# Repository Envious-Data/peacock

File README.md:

# Peacock

Peacock is an RP2040 powered trackpad running QMK. It features an integrated Microchip MaxTouch sensor IC which is
connected to a 7" capacitive sensor.

This repo contains a fork of George Norton's project which I have modified to be a single PCB without the keyboard switches and encoders, I dont have the knowledge to have done this project myself hence why I have forked George's project.

## Features
- Fully PCBA, this other than switches and encoders, this board is designed to be fully factory assembled.
- Integrated RP2040 controller, no need to a separate controller.
- 7 inch 16:9 capacitive sensor.

## But how does it work?
The capacitive sensing IC is wired to a grid of diamond shaped electrodes. The diamonds are connected to form rows and columns. The IC scans the matrix by
applying a small voltage to the rows in turn, and then measuring voltage on the columns. Any conductive objects nearby (like your finger) will distrupt the
electrical field and can be detected.

## Software limitations
QMK currently supports pointing devices, but it reports them as USB hid mice. This means we only report a single pointer movement, a pair of scroll wheels and
a set of buttons to the host. For now, this prevents us from supporting some multitouch gestures such as pinch to zoom.

## Firmware
Peacock support has not yet been merged back to QMK. You can find a branch [here](https://github.com/george-norton/qmk_firmware/tree/peacock).

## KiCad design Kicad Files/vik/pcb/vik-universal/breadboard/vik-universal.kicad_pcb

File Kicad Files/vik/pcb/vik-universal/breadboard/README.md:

# VIK universal (breadboard)

## Overview

This is a simple pcb that allows you to connect any series of up to 12 pin headers to a VIK connector, in any order.

You solder one of the numbered through holes to a column. Be careful not to solder multiple signals from the 3rd party board to the same VIK signal (each column). Each column of through holes (except the numbered ones on the left or right) are all wired together.

## Fabrication and BOM

For PCB fabrication, you can use the files in the production folder.

* gerbers.zip - the file used to fabricate the pcb
* bom.csv - used for PCBA. You can also use the part numbers in this file to look up the exact parts as [lcsc.com](https://lcsc.com)
* positions.csv - used for PCBA

Using the 3 files above, this has been tested at [jlcpcb.com](https://jlcpcb.com)

## VIK module certification

| Category                | Classification          | Response           |
| ----------------------- | ----------------------- | ------------------ |
| FPC connector           | Required                | :heavy_check_mark: |
| Breakout pins           | Recommended             | :heavy_check_mark: |
| Uses: SPI               | Optional                | N/A                |
| SPI used for SPI only   | Strongly recommended    | N/A                |
| Uses: I2C               | Optional                | N/A                |
| I2C used for I2C only   | Strongly Recommended    | N/A                |
| I2C pull ups            | Required                | N/A                |
| Uses: RGB               | Optional                | N/A                |
| Uses: Extra GPIO 1      | Optional                | N/A                |
| Uses: Extra GPIO 2      | Optional                | N/A                |
| Standard PCB Size/Mount | Strongly recommended    | :x:                |

## PCB images

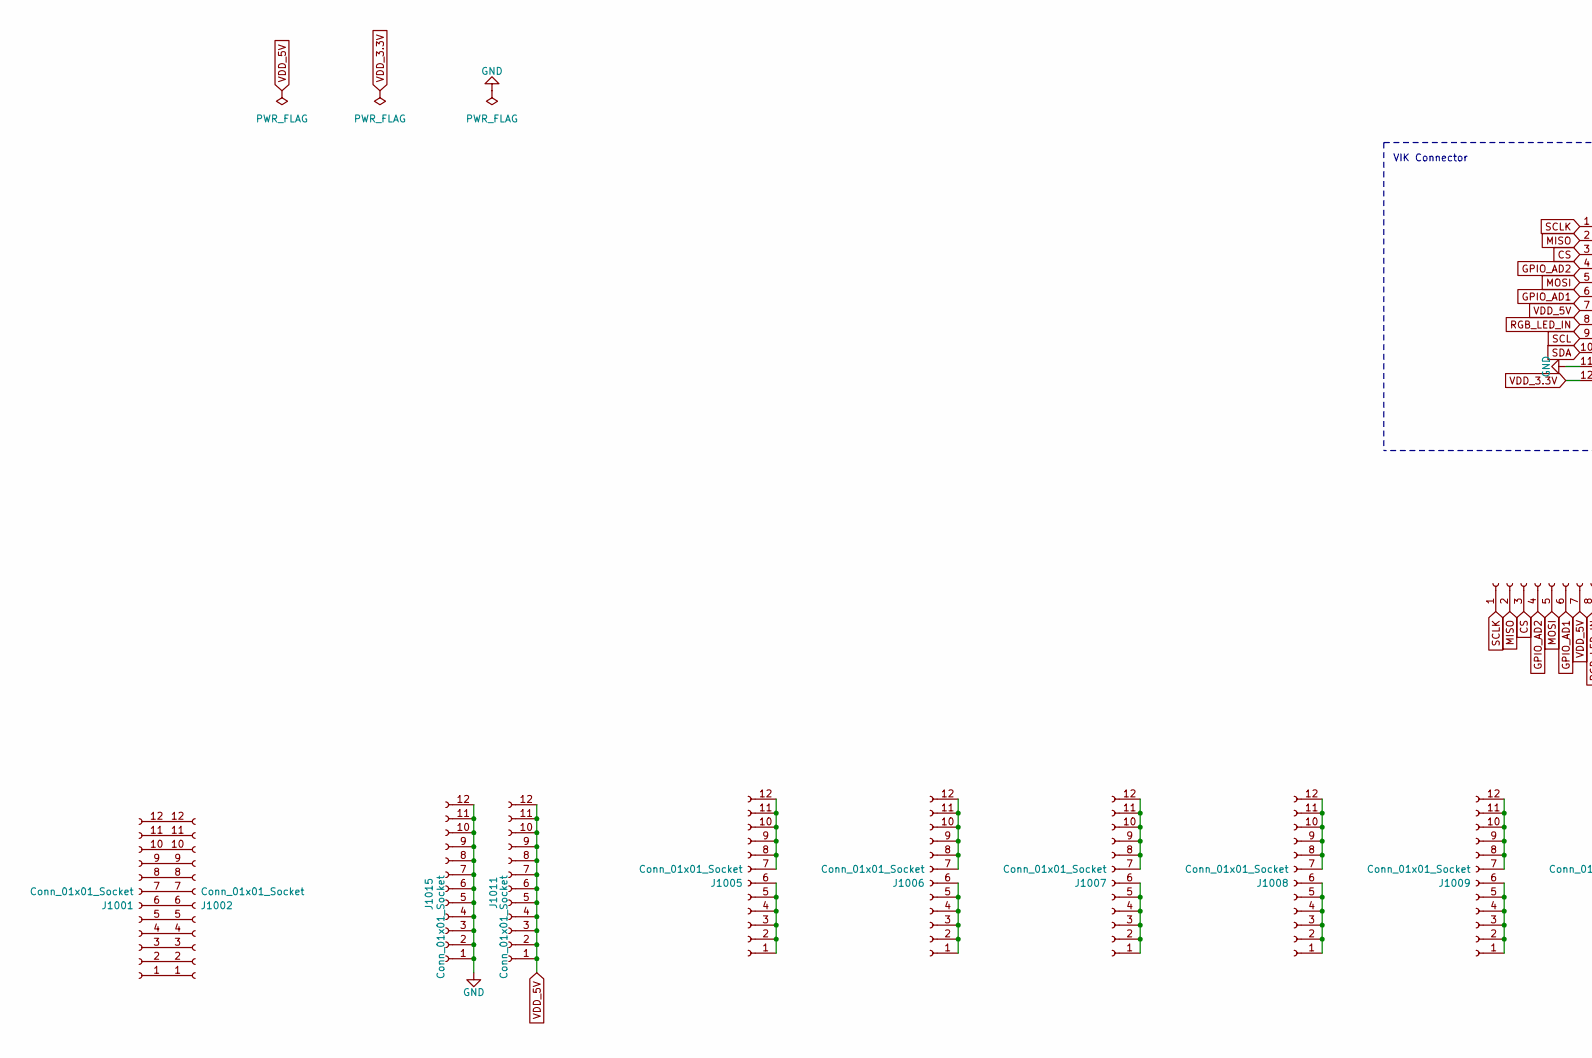
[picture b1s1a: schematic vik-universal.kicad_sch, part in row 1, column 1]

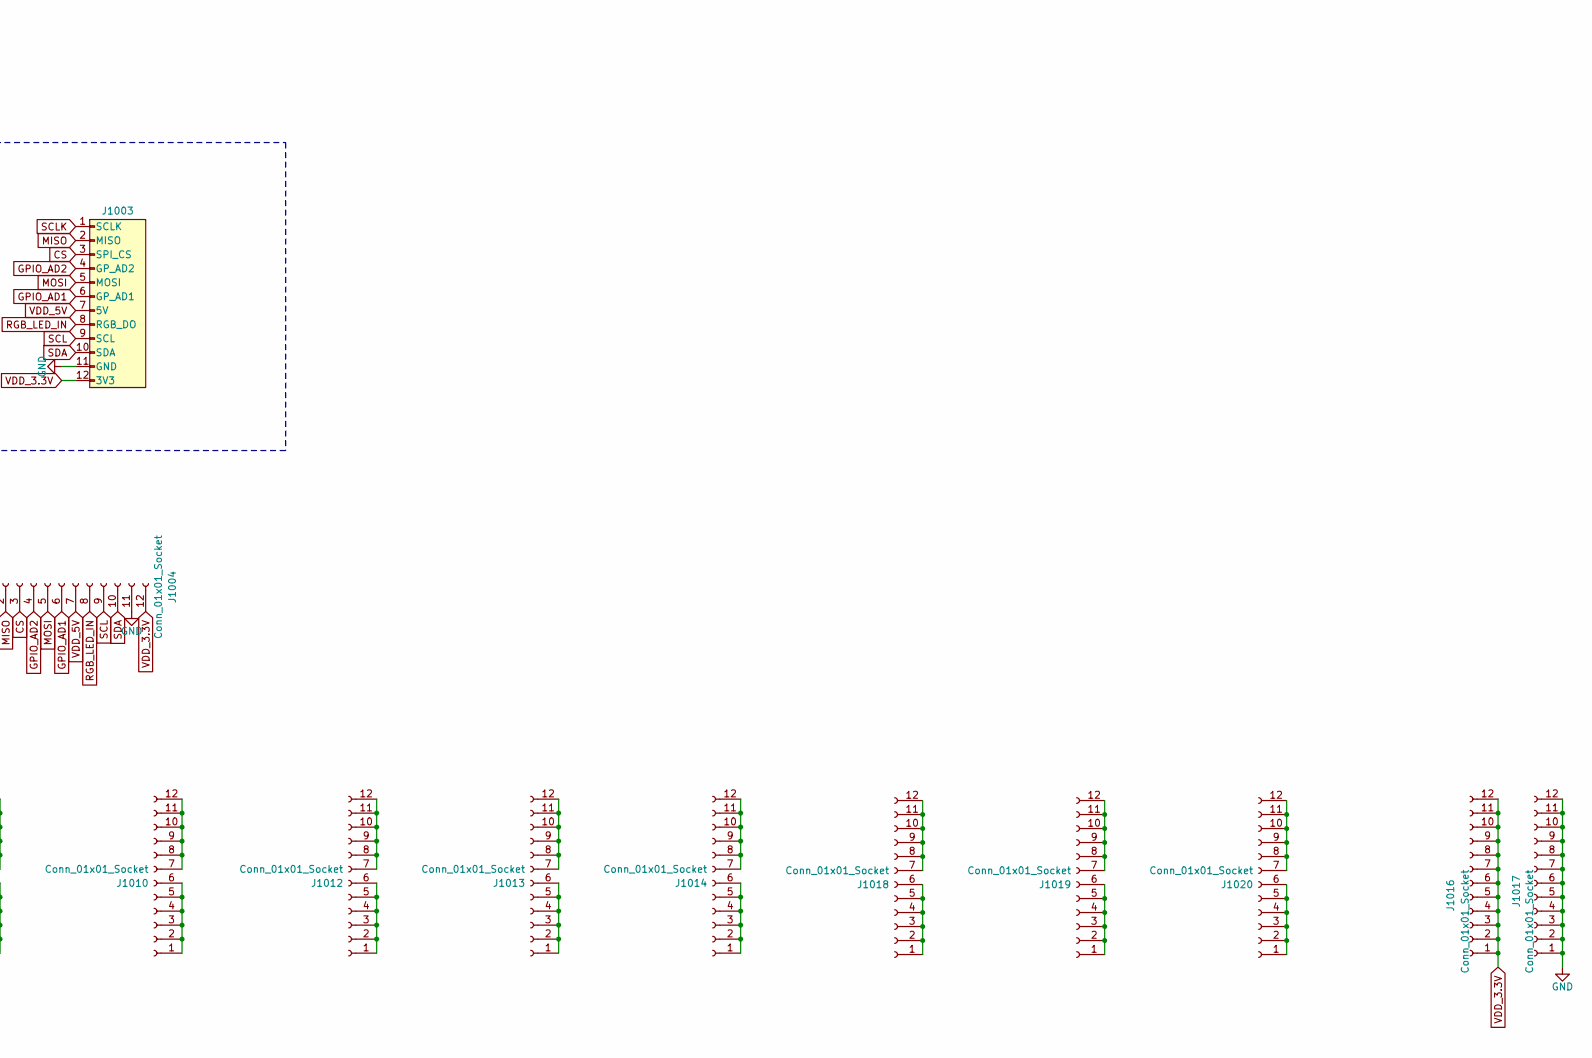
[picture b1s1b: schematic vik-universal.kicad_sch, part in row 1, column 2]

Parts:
J1001, J1002: Conn_01x01_Socket; PinSocket_1x12_P2.54mm_Vertical_NoSilk
J1003: vik-module-connector-horizontal; LCSC C2919557
J1004: Conn_01x01_Socket; PinSocket_1x12_P2.54mm_Vertical_IndividualSilk
J1005, J1006, J1007, J1008, J1009, J1010, J1012, J1013, J1014, J1018, J1019, J1020: Conn_01x01_Socket; PinSocket_1x12_P2.54mm_Vertical_6x6_SplitSilk
J1011, J1015, J1016, J1017: Conn_01x01_Socket; PinSocket_1x12_P2.54mm_Vertical_FullSilk

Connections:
CS: J1003.3 (SPI_CS), J1004.3
GND: J1003.11 (GND), J1004.11, J1015.1, J1015.2, J1015.3, J1015.4, J1015.5, J1015.6, J1015.7, J1015.8, J1015.9, J1015.10, J1015.11, J1015.12, J1017.1, J1017.2, J1017.3, J1017.4, J1017.5, J1017.6, J1017.7, J1017.8, J1017.9, J1017.10, J1017.11, J1017.12
GPIO_AD1: J1003.6 (GPIO_AD1), J1004.6
GPIO_AD2: J1003.4 (GPIO_AD2), J1004.4
MISO: J1003.2 (MISO), J1004.2
MOSI: J1003.5 (MOSI), J1004.5
unnamed: J1001.1, J1002.1
unnamed: J1001.2, J1002.2
unnamed: J1001.3, J1002.3
unnamed: J1001.4, J1002.4
unnamed: J1001.5, J1002.5
unnamed: J1001.6, J1002.6
unnamed: J1001.7, J1002.7
unnamed: J1001.8, J1002.8
unnamed: J1001.9, J1002.9
unnamed: J1001.10, J1002.10
unnamed: J1001.11, J1002.11
unnamed: J1001.12, J1002.12
unnamed: J1005.1, J1005.2, J1005.3, J1005.4, J1005.5, J1005.6
unnamed: J1005.7, J1005.8, J1005.9, J1005.10, J1005.11, J1005.12
unnamed: J1006.1, J1006.2, J1006.3, J1006.4, J1006.5, J1006.6
unnamed: J1006.7, J1006.8, J1006.9, J1006.10, J1006.11, J1006.12
unnamed: J1007.1, J1007.2, J1007.3, J1007.4, J1007.5, J1007.6
unnamed: J1007.7, J1007.8, J1007.9, J1007.10, J1007.11, J1007.12
unnamed: J1008.1, J1008.2, J1008.3, J1008.4, J1008.5, J1008.6
unnamed: J1008.7, J1008.8, J1008.9, J1008.10, J1008.11, J1008.12
unnamed: J1009.1, J1009.2, J1009.3, J1009.4, J1009.5, J1009.6
unnamed: J1009.7, J1009.8, J1009.9, J1009.10, J1009.11, J1009.12
unnamed: J1010.1, J1010.2, J1010.3, J1010.4, J1010.5, J1010.6
unnamed: J1010.7, J1010.8, J1010.9, J1010.10, J1010.11, J1010.12
unnamed: J1012.1, J1012.2, J1012.3, J1012.4, J1012.5, J1012.6
unnamed: J1012.7, J1012.8, J1012.9, J1012.10, J1012.11, J1012.12
unnamed: J1013.1, J1013.2, J1013.3, J1013.4, J1013.5, J1013.6
unnamed: J1013.7, J1013.8, J1013.9, J1013.10, J1013.11, J1013.12
unnamed: J1014.1, J1014.2, J1014.3, J1014.4, J1014.5, J1014.6
unnamed: J1014.7, J1014.8, J1014.9, J1014.10, J1014.11, J1014.12
unnamed: J1018.1, J1018.2, J1018.3, J1018.4, J1018.5, J1018.6
unnamed: J1018.7, J1018.8, J1018.9, J1018.10, J1018.11, J1018.12
unnamed: J1019.1, J1019.2, J1019.3, J1019.4, J1019.5, J1019.6
unnamed: J1019.7, J1019.8, J1019.9, J1019.10, J1019.11, J1019.12
unnamed: J1020.1, J1020.2, J1020.3, J1020.4, J1020.5, J1020.6
unnamed: J1020.7, J1020.8, J1020.9, J1020.10, J1020.11, J1020.12
RGB_LED_IN: J1003.8 (RGB_LED_IN), J1004.8
SCL: J1003.9 (SCL), J1004.9
SCLK: J1003.1 (SCLK), J1004.1
SDA: J1003.10 (SDA), J1004.10
VDD_3.3V: J1003.12 (3V3), J1004.12, J1016.1, J1016.2, J1016.3, J1016.4, J1016.5, J1016.6, J1016.7, J1016.8, J1016.9, J1016.10, J1016.11, J1016.12
VDD_5V: J1003.7 (5V), J1004.7, J1011.1, J1011.2, J1011.3, J1011.4, J1011.5, J1011.6, J1011.7, J1011.8, J1011.9, J1011.10, J1011.11, J1011.12

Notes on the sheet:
VIK Connector

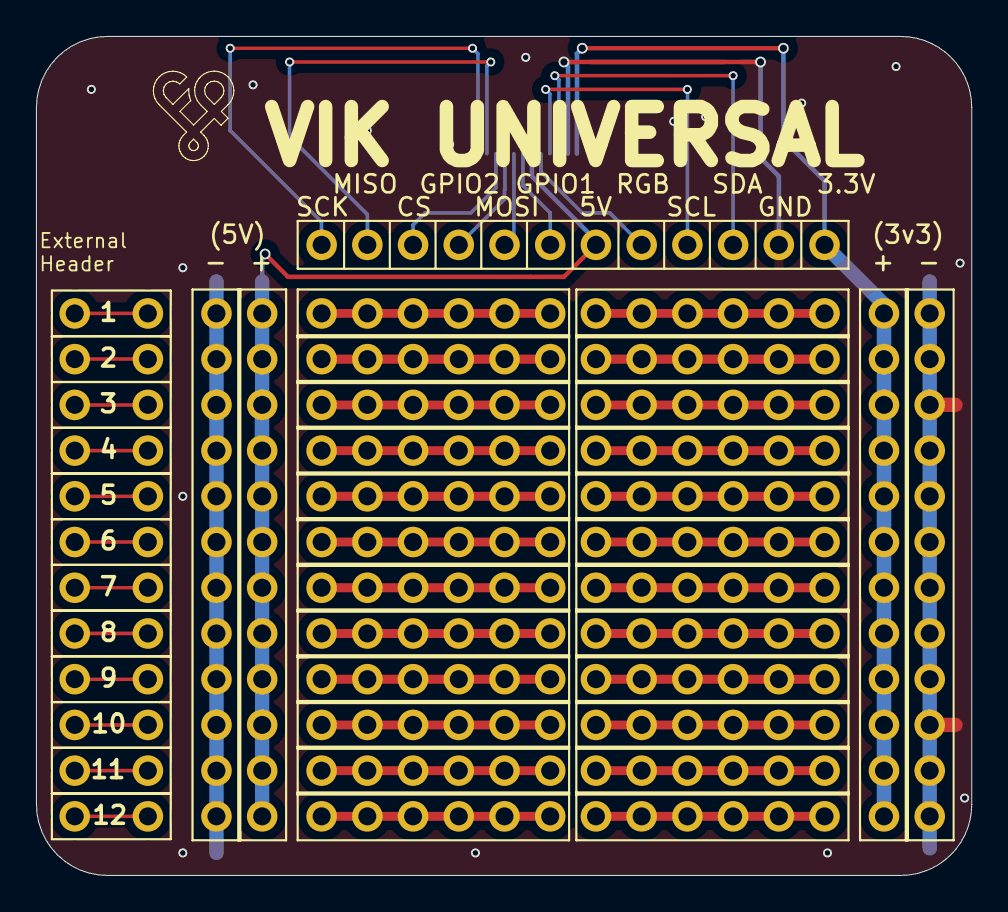
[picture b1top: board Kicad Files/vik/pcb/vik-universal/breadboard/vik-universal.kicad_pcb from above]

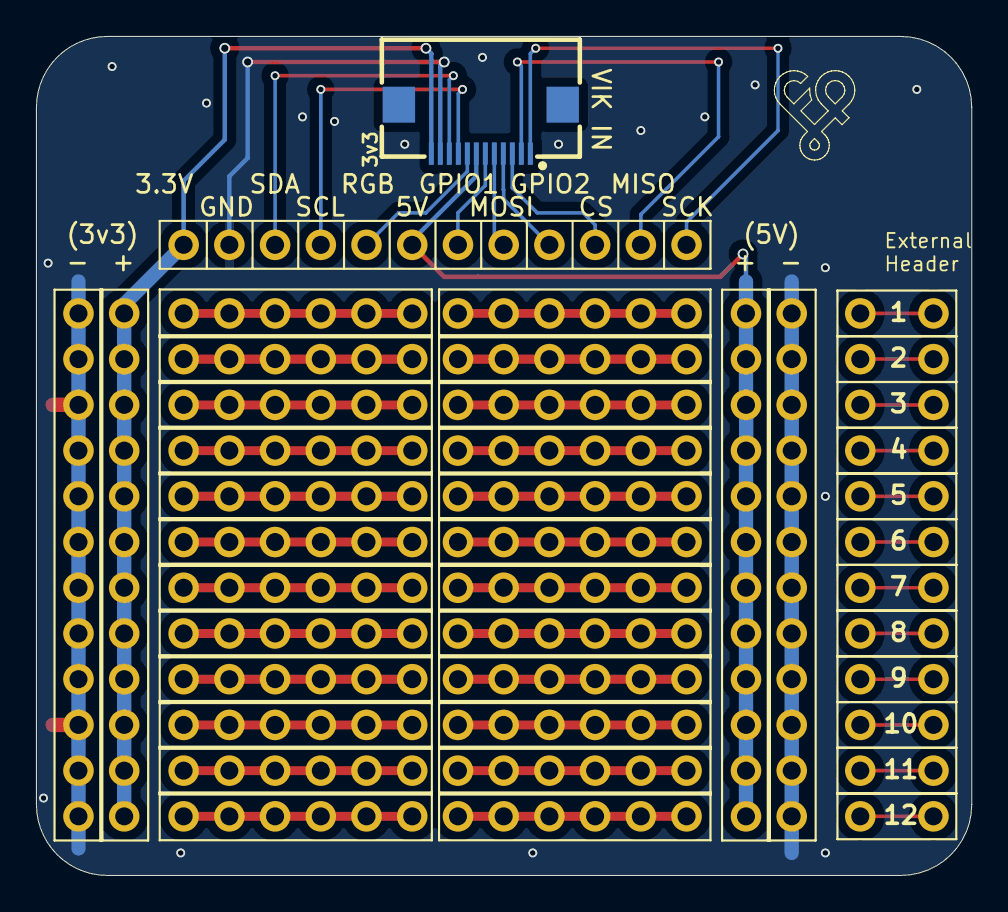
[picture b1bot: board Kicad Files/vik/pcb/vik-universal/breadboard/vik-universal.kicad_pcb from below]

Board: 2 copper layers, 52.0 x 46.6 mm, 20 parts (2 on the bottom side), 48 nets.

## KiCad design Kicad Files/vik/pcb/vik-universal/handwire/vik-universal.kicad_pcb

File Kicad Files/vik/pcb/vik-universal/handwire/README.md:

# VIK universal (handwire)

## Overview

This is a simple pcb that allows you to connect any series of up to 12 pin headers to a VIK connector, in any order.

You wire 1 through hole from the bottom to one from the top, which connects a 3rd party module or board to any VIK signal you want.

## Fabrication and BOM

For PCB fabrication, you can use the files in the production folder.

* gerbers.zip - the file used to fabricate the pcb
* bom.csv - used for PCBA. You can also use the part numbers in this file to look up the exact parts as [lcsc.com](https://lcsc.com)
* positions.csv - used for PCBA

Using the 3 files above, this has been tested at [jlcpcb.com](https://jlcpcb.com)

## VIK module certification

| Category                | Classification          | Response           |
| ----------------------- | ----------------------- | ------------------ |
| FPC connector           | Required                | :heavy_check_mark: |
| Breakout pins           | Recommended             | :heavy_check_mark: |
| Uses: SPI               | Optional                | N/A                |
| SPI used for SPI only   | Strongly recommended    | N/A                |
| Uses: I2C               | Optional                | N/A                |
| I2C used for I2C only   | Strongly Recommended    | N/A                |
| I2C pull ups            | Required                | N/A                |
| Uses: RGB               | Optional                | N/A                |
| Uses: Extra GPIO 1      | Optional                | N/A                |
| Uses: Extra GPIO 2      | Optional                | N/A                |
| Standard PCB Size/Mount | Strongly recommended    | :x:                |

## PCB images

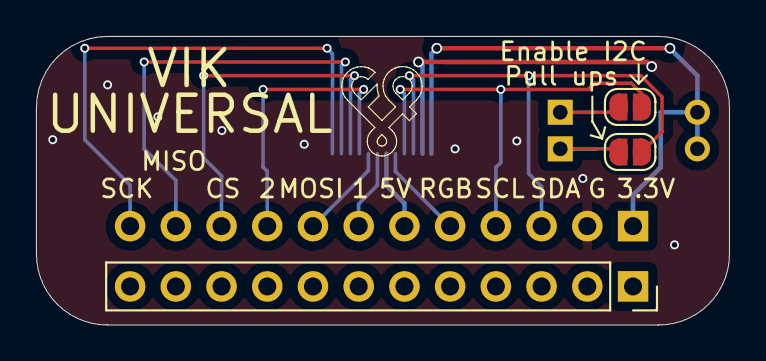
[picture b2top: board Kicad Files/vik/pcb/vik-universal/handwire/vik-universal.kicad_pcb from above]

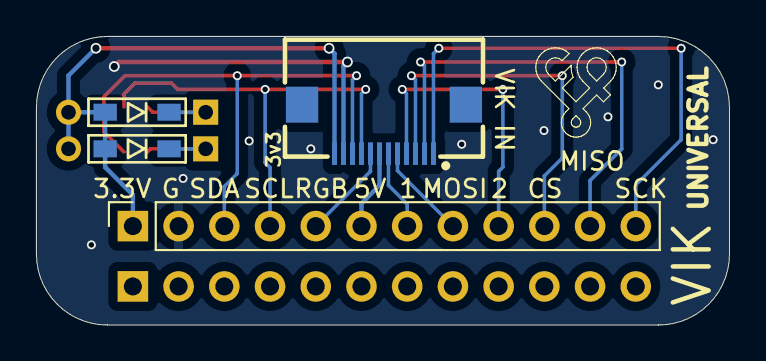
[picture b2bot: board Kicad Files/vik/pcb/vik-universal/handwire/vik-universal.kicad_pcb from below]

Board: 2 copper layers, 38.5 x 16.0 mm, 7 parts (4 on the bottom side), 14 nets.

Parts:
J1001, J1002: Conn_01x01_Socket; PinSocket_1x12_P2.54mm_Vertical
J1003: vik-module-connector-horizontal
JP1001, JP1002: SolderJumper_2_Open; SolderJumper-2_P1.3mm_Open_RoundedPad1.0x1.5mm
R1001, R1002: 4.7k; D3_TH_SMD

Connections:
CS: J1001.10, J1003.3 (SPI_CS)
GND: J1001.2, J1003.11 (GND)
GPIO_AD1: J1001.7, J1003.6 (GPIO_AD1)
GPIO_AD2: J1001.9, J1003.4 (GPIO_AD2)
MISO: J1001.11, J1003.2 (MISO)
MOSI: J1001.8, J1003.5 (MOSI)
unnamed: JP1001.2 (B), R1001.1
unnamed: JP1002.2 (B), R1002.1
RGB_LED_IN: J1001.5, J1003.8 (RGB_LED_IN)
SCL: J1001.4, J1003.9 (SCL), JP1001.1 (A)
SCLK: J1001.12, J1003.1 (SCLK)
SDA: J1001.3, J1003.10 (SDA), JP1002.1 (A)
VDD_3.3V: J1001.1, J1003.12 (3V3), R1001.2, R1002.2
VDD_5V: J1001.6, J1003.7 (5V)

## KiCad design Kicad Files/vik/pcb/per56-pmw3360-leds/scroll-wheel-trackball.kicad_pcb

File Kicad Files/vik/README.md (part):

# VIK

> **Warning**  
> This is a work in progress. It has been tested to be functional, but please consult **sadekbaroudi** in the **#vik** channel of the [fingerpunch discord server](https://fingerpunch.xyz/discord) if you'd like to design a keyboard or module.

> **Note**  
> **To see the list of known supported keyboards and modules, go to [this section](#known-list-of-vik-certifications) at the bottom of the readme**

> **Note**  
> Please be aware that for keyboard pcbs, VIK assumes that it's running at 3.3v logic levels. This is easily achieved by using a RP2040. If you are using a 5v controller, it is the keyboard's responsibility to level shift before going to the VIK module. See the [Microcontroller selection](#microcontroller-selection) section below

## Overview

VIK is a standard for a data interface between printed circuit boards. It is intended to provide modularity between a mechanical keyboard pcb and additional features. The main pcb can have a controller and a switch matrix, while the modules can provide additional features.

The standard specifies the following:
1. The type of connector
2. The signals mapped to each pin on the connector
3. The type of cable
4. (optional) The size of the module pcb and mounting hole locations
5. Inclusion of the VIK logo on the PCB

> **Note**  
> Adding support for VIK is as simple as adding a symbol and footprint, provided in this repository, followed by some basic wiring. If you want to jump straight to the guide to do this using Kicad, go to [Implementation with Kicad](#implementation-with-kicad) 

## Renders

Keyboard with VIK certification using the keyboard footprint

Module with VIK certification using the module footprint

### What value does this bring?

#### Consoldiates efforts for feature design

In a community full of talented people doing lots of innovation, we are seeing a plethora of new options for keyboard layout configurations, features, etc. With all this innovation, we're doing very little to share our efforts.

For example, if one person invests in adding support for a trackball with a scroll wheel, others have to identify how to do that, and add support for their keyboard design.

#### Ease of upgrades

With VIK support, upgrading your features is as simple as getting a new VIK module, and swapping it out.

Let's say you built a keyboard with an integrated trackpad, and you love it. Months after setting it up, you realize that you'd love to have a trackball and haptic feedback. Now you need to design a new pcb (or find someone who has) with the features you'd like. Most people don't know how, or don't want to put forth this effort, so they will settle for their current configuration. With much less effort, you can create a new VIK module, assemble it, and connect to your existing keyboard.

#### One feature for many keyboard layouts

One of the biggest challengs I find, is that a keyboard may have some really excellent features, but I really don't like the key layout. In that case, I won't be interested in the keyboard, despite wanting the features.

Provided that keyboard designers adopt the VIK standard on the main keyboard pcb, the modules are usable on any of those keyboards. So, you can design or find a keyboard that has your preferred layout, and then add the features that you like. True customizability for the exact keyboard you want to use.

## Specifications

There are two things that must be implemented for this to be successful. The keyboard pcb must support the VIK interface, and the module pcb must support the VIK interface

### Connector

The required connector is a FPC 12 pin 0.5mm pitch connector. It should be available on both the keyboard pcb and the module pcb.

### Cable

The cable should be a 12 pin 0.5mm pitch FPC Type A cable (leads are exposed on the same side).

The specs below state that you must invert the connector pin order between the keyboard and the module, which means Type A is required.

### Interface

The interface includes the following signals:
* 3.3V
* GND
* SDA
* SCL
* RGB Data Out
* 5V
* Digital/Analog GPIO 1
* MOSI
* Digital/Analog GPIO 2
* SPI CS
* MISO
* SCLK

The order specified above is the order they should be used on the FPC connector on the **keyboard side**, pins 1 through 12. For the module pcbs, they should be inverted, since the cable will automatically invert the order when connected. If you use the VIK Kicad symbols and footprints, this is managed for you. See the [Implementation with Kicad](#implementation-with-Kicad) section below

### VIK logo

So long as you adhere to the specs above, you can consider your keyboard pcb or module VIK enabled. The last thing you do before publishing or manufacturing your PCB is to include the VIK logo.

There are a collection of logos you can use in the kicad/vik.pretty directory of this repository, all prefixed with `vik-logo`. For instance, you could take the pre-made kicad footprints and include them on your pcb. If you aren't using kicad, there is a dxf and svg you can use as well.

## Module PCB shape and mounting

This is optional, but highly recommended. By adhereing to a standard size and mounting, this will allow others to design keyboard pcbs and/or cases that will support mounting a variety of modules.

There are two specs, a small and large pcb.

**All mounting holes should fit M2 screws**

### Small PCB

Size: less than 25mm by 42mm

Mounting: 2 mounting holes

### Large PCB

Size: less than 65mm by 65mm

Mounting: 4 mounting holes

The mounting holes should 44.5mm apart in a square, centered around the center of the pcb. Alternatively, you can place these mounting holes evenly distributed around a 63mm circle, also centered around the center of the pcb.

### Module mounting Kicad footprints

There are two mounting footprints, found in the vik.pretty footprints folder:
* vik-module-mounting-small
* vik-module-mounting-large

You can use these for one of two purposes:
1) When creating a module, use the footprint to ensure that your module pcb has the correct mounting locations
2) When creating a keyboard, use the footprint to position where you'd like to mount a module pcb

You can use the Mounting Hole symbol in the schematic, and associate one of the footprints as shown below:

## Implementation with Kicad

Given Kicad's popularity, I've made it (hopefully) very convenient to implement VIK on the keyboard and module side.

### Add symbols and footprints to your Kicad project

1. Clone this repository to your local machine
2. Add the VIK symbol library your project
3. Add the VIK footprint library to your project

Please note that the path in the screenshots won't be the same as yours. It should be:  
`{PATH TO CLONE OF THIS REPO}/kicad/vik.kicad_sym`  
and  
`{PATH TO CLONE OF THIS REPO}/kicad/vik.pretty`  

### Kicad keyboard connector

1. Add a new symbol in the schematic, and select the `vik-keyboard-connector`
2. Connect all the signals as specified
3. Associate with the type of footprint you'd like to use (all of the VIK examples use the horizontal connector footprint). Given you are making a keyboard connector, be sure to use the ones that have the word keyboard in them. See the image below for an example.
4. Update your PCB from the schematic and wire it up!

#### Adding the keyboard connector symbol

#### Assigning the keyboard connector footprint

#### Example schematic for keyboard connector

#### Example wiring for keyboard connector

### Kicad module connector

1. Add a new symbol in the schematic, and select the `vik-module-connector`
2. Connect all the signals as specified
3. Associate with the type of footprint you'd like to use (all of the VIK examples use the horizontal connector footprint). Given you are making a module connector, be sure to use the ones that have the word module in them. See the image below for an example.
4. Update your PCB from the schematic and wire it up!

#### Adding the module connector symbol

#### Assigning the module connector footprint

#### Example schematic for module connector

#### Example wiring for module connector

## Schematic design guide

Assuming you already have the VIK symbols and footprints included in your schematic, you will need to wire them according to the specs. Let's walk through each signal, and review how to wire. I'll break this into two parts, one for the keyboard design, and one for the module design.

### Keyboard schematic guide

First and foremost, it's very important that the keyboard have everything set up correctly. Given it's the one supplying the signals to the module, you want to be fully compatible with as many modules as possible.

Here is each signal, and an overview of how to wire it.

**3.3V**

This one is fairly straight forward in the sense that you just need to supply 3.3v. That said, there are controllers out there that do not include it natively. Please review the [Microcontroller selection](#Microcontroller-selection) section below for details.

**GND**

Connect ground to this pin.

**SDA**

Microcontrollers usually have more than one set of I2C signals. On dev boards like the [Helios](https://github.com/0xCB-dev/0xCB-Helios) or [Elite-Pi](https://docs.keeb.io/elite-pi-guide), it's as simple as wiring the SDA pin to the corresponding SDA pin on the VIK connector.

**SCL**

This is the exact same as described for SDA, but using SCL instead

**RGB Data Out**

If you don't have RGB leds on your keyboard, this can be any digital GPIO. Just pick any data signal, and route it to the RGB pin on the VIK connector.

If you are using RGB leds, you'll want to do two things:
1. Wire the data out from the last LED to the RGB pin on the VIK connector
2. Connect from the controller LED data pin to the VIK connector, but put an open jumper in the middle. The nice thing about this is that it allows the end user to still use the LED feature on a module without necessarily having the LEDs assembled on their keyboard.

**5V**

Connect 5V to the VIK connector. Be careful not to use VCC on an RP2040 controller, as that is 3.3V. Instead, you can take the RAW output from a controller. On all controllers that I'm aware of as of this writing, it's the top right pin (please double check this before you wire it up).

For example, on the elite-pi:

**Digital/Analog GPIO 1**

Similar to the RGB Data Out, you can select any pin, but it should support both digital and analog. Below is an example of the Elite-Pi, highlighting its pins that support both.

**MOSI**

Similar to I2C, SPI has predefined locations on most controllers. If doing an integrated controller, please refer to the datasheet to determine the correct pins.

That said, on dev controllers like the [Helios](https://github.com/0xCB-dev/0xCB-Helios) or [Elite-Pi](https://docs.keeb.io/elite-pi-guide), they are standard locations. See the image below. You can wire the 4 SPI pins as shown.

**Digital/Analog GPIO 2**

Same as `Digital/Analog GPIO 1`, but this should be a second independent GPIO of the same specifications.

**SPI CS**

No additional info beyond the `MOSI` section above. Same course of action, but for the SPI CS signal.

**MISO**

No additional info beyond the `MOSI` section above. Same course of action, but for the MISO signal.

**SCLK**

No additional info beyond the `MOSI` section above. Same course of action, but for the SCLK signal.

### Module schematic guide

There aren't any major considerations for the schematic for the module. Everything on the connector is an input, so you can choose what to do with them.

That said, please note that using the I2C or SPI pins for anything **other than I2C or SPI** will break on keyboards that use those signals on the main board. So, please avoid doing so if you care about maximizing compatibility.

## Design guidelines and recommendations

### Reference designs

For the keyboard side, I created a keyboard called [vulpes minora](http://github.com/sadekbaroudi/vulpes-minora). This keyboard has been manufactured and tested to work with VIK modules.

For the module side, please see the pcb directory in this repository. Each subdirectory within it has a module that you can review to see how these are implemented.

### I2C guidelines

#### Keyboard pcb

As mentioned above, the responsibility of using pull up resistors is on the VIK modules. This may cause challenges for a few reasons. You may want (or need) to use I2C on the main keyboard PCB, which means you need to use pull up resistors. If this is the case, please provide instructions to inform the users that when using VIK modules, they will need to remove (or not place) the pull up resistor on the keyboard.

#### Module pcb

When designing a module, please ensure that you include pull up resistors, since the guidelines state that the keyboard pcb is not responsible for it.

### Microcontroller selection

If you are designing a keyboard pcb that uses a dev board as a controller (e.g. pro micro, elite-c, stemcell, etc), you should consider that the VIK specs calls for 3.3V and 5V. Given these controllers operate on 5V and don't provide 3.3V, you won't be able to use them for VIK compatibility without additonal circuitry to convert 5V to 3.3V.

**As described at the top of the README in the note, the keyboard pcb should run at at 3.3v logic levels. The simplest option is to use a RP2040 based development board. For integrated controllers, either use a controller that already runs at 3.3v logic, or level shift the GPIO before going into the VIK connector.**

Some options include:
1. Support only RP2040 based controllers (e.g. splinky, elite-pi, helios), where VCC is 3.3V, and the RAW pin provides 5V
2. Support other 5V controllers, and use something like an LDO to convert 5V to 3.3V for the VIK 3.3V signal and GPIO signals
3. Anything you want, as long as you can provide 5V and 3.3V (both power and 3.3v gpio logic levels)

The vulpes minora is an example of point number 1 above.

## VIK certification

In order to be VIK certified, you should be compliant with everything above, and have your keyboard or module reviewed. Upon review, the reviewer will make a card for your pcb, as explained below.

### VIK keyboard certification card

#### Descriptions

* **FPC connector:** has the correct FPC connector with the right pinout, and is wired to specificaton. See the connectors in the kicad/vik.pretty directory
* **Breakout pins:** includes breakout pins using the [VIK breakout pin footprint](https://github.com/sadekbaroudi/vik/blob/master/kicad/vik.pretty/vik-keyboard-throughole.kicad_mod), or has through holes for all the signals. This allows easy access to all the signals. Also, the footprint is compatible with a [hand solderable FPC breakout board](https://www.amazon.com/uxcell-Converter-Couple-Extend-Adapter/dp/B07RVD1J1K).
* **Supplies: SPI** supplies SPI signals, including MISO, MOSI, SCLK, and CS
* **Supplies: I2C:** supplies I2C, including SDA and SCL
* **I2C on main PCB:** Does the main PCB use any I2C already. Valid responses are `yes` or `no`. If this is true, the `I2C pull ups` field must have a value
* **I2C pull ups:** I2C pull up resistor value, :x: if no pull ups on the main pcb, or resistor value if present
* **Supplies: RGB:** supplies RGB data out
* **Supplies: Extra GPIO 1:** supplies the extra GPIO, response will be one of: (**:x: | Digital Only | Analog/Digital**)
* **Supplies: Extra GPIO 2:** supplies the extra GPIO, response will be one of: (**:x: | Digital Only | Analog/Digital**)

#### Keyboard sample cards

Example of a failing card:

| Category                 | Classification          | Response           |
| -----------------------  | ----------------------- | ------------------ |
| FPC connector            | Required                | :heavy_check_mark: |
| Breakout pins            | Recommended             | :x:                |
| Supplies: SPI            | Required                | :heavy_check_mark: |
| Supplies: I2C            | Required                | :heavy_check_mark: |
| I2C on main PCB          | Discouraged             | yes                |
| I2C pull ups             | Informative             | 2.2kΩ              |
| Supplies: RGB            | Required                | :x:                |
| Supplies: Extra GPIO 1   | Required                | :x:                |
| Supplies: Extra GPIO 2   | Required                | :x:                |

A "perfect" keyboard card would look like this:

| Category                 | Classification          | Response           |
| -----------------------  | ----------------------- | ------------------ |
| FPC connector            | Required                | :heavy_check_mark: |
| Breakout pins            | Recommended             | :heavy_check_mark: |
| Supplies: SPI            | Strongly recommended    | :heavy_check_mark: |
| Supplies: I2C            | Strongly recommended    | :heavy_check_mark: |
| I2C on main PCB          | Discouraged             | no                 |
| I2C pull ups             | Informative             | N/A                |
| Supplies: RGB            | Strongly recommended    | :heavy_check_mark: |
| Supplies: Extra GPIO 1   | Required                | Analog/Digital     |
| Supplies: Extra GPIO 2   | Required                | Analog/Digital     |

### VIK module certification card

#### Descriptions

* **FPC connector:** has the correct FPC connector with the right pinout, and is wired to specificaton. See the connectors in the kicad/vik.pretty directory
* **Breakout pins:** includes breakout pins using the [VIK breakout pin footprint](https://github.com/sadekbaroudi/vik/blob/master/kicad/vik.pretty/vik-keyboard-throughole.kicad_mod), or has through holes for all the signals. This allows easy access to all the signals. Also, the footprint is compatible with a [hand solderable FPC breakout board](https://www.amazon.com/uxcell-Converter-Couple-Extend-Adapter/dp/B07RVD1J1K).
* **Uses: SPI:** the module is utilizing SPI
* **SPI used for SPI only:** if you are using any of the SPI gpio for any purpose other than SPI, this will remain unchecked. This means that keyboard pcbs that use SPI will be incompatible with this module.
* **Uses: I2C:**
* **I2C used for I2C only:** if you are using any of the I2C gpio for any purpose other than I2C, this will remain unchecked. This means that keyboard pcbs that use I2C will be incompatible with this module.
* **I2C pull ups:** I2C pull up resistor value, if applicable. These are only required if I2C is being used on the module.
* **Uses: RGB:** uses RGB data out
* **Uses: Extra GPIO 1:** uses the extra GPIO, response will be one of: (**:x: | Digital Only | Analog/Digital**)
* **Uses: Extra GPIO 2:** uses the extra GPIO, response will be one of: (**:x: | Digital Only | Analog/Digital**)
* **Standard PCB Size/Mount:** adheres to standard module size and mounts, responses will be one of: (**:x: | Small | Large**)

#### Module sample card

General example:

| Category                | Classification          | Response           |
| ----------------------- | ----------------------- | ------------------ |
| FPC connector           | Required                | :heavy_check_mark: |
| Breakout pins           | Recommended             | :x:                |
| Uses: SPI               | Optional                | :heavy_check_mark: |
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
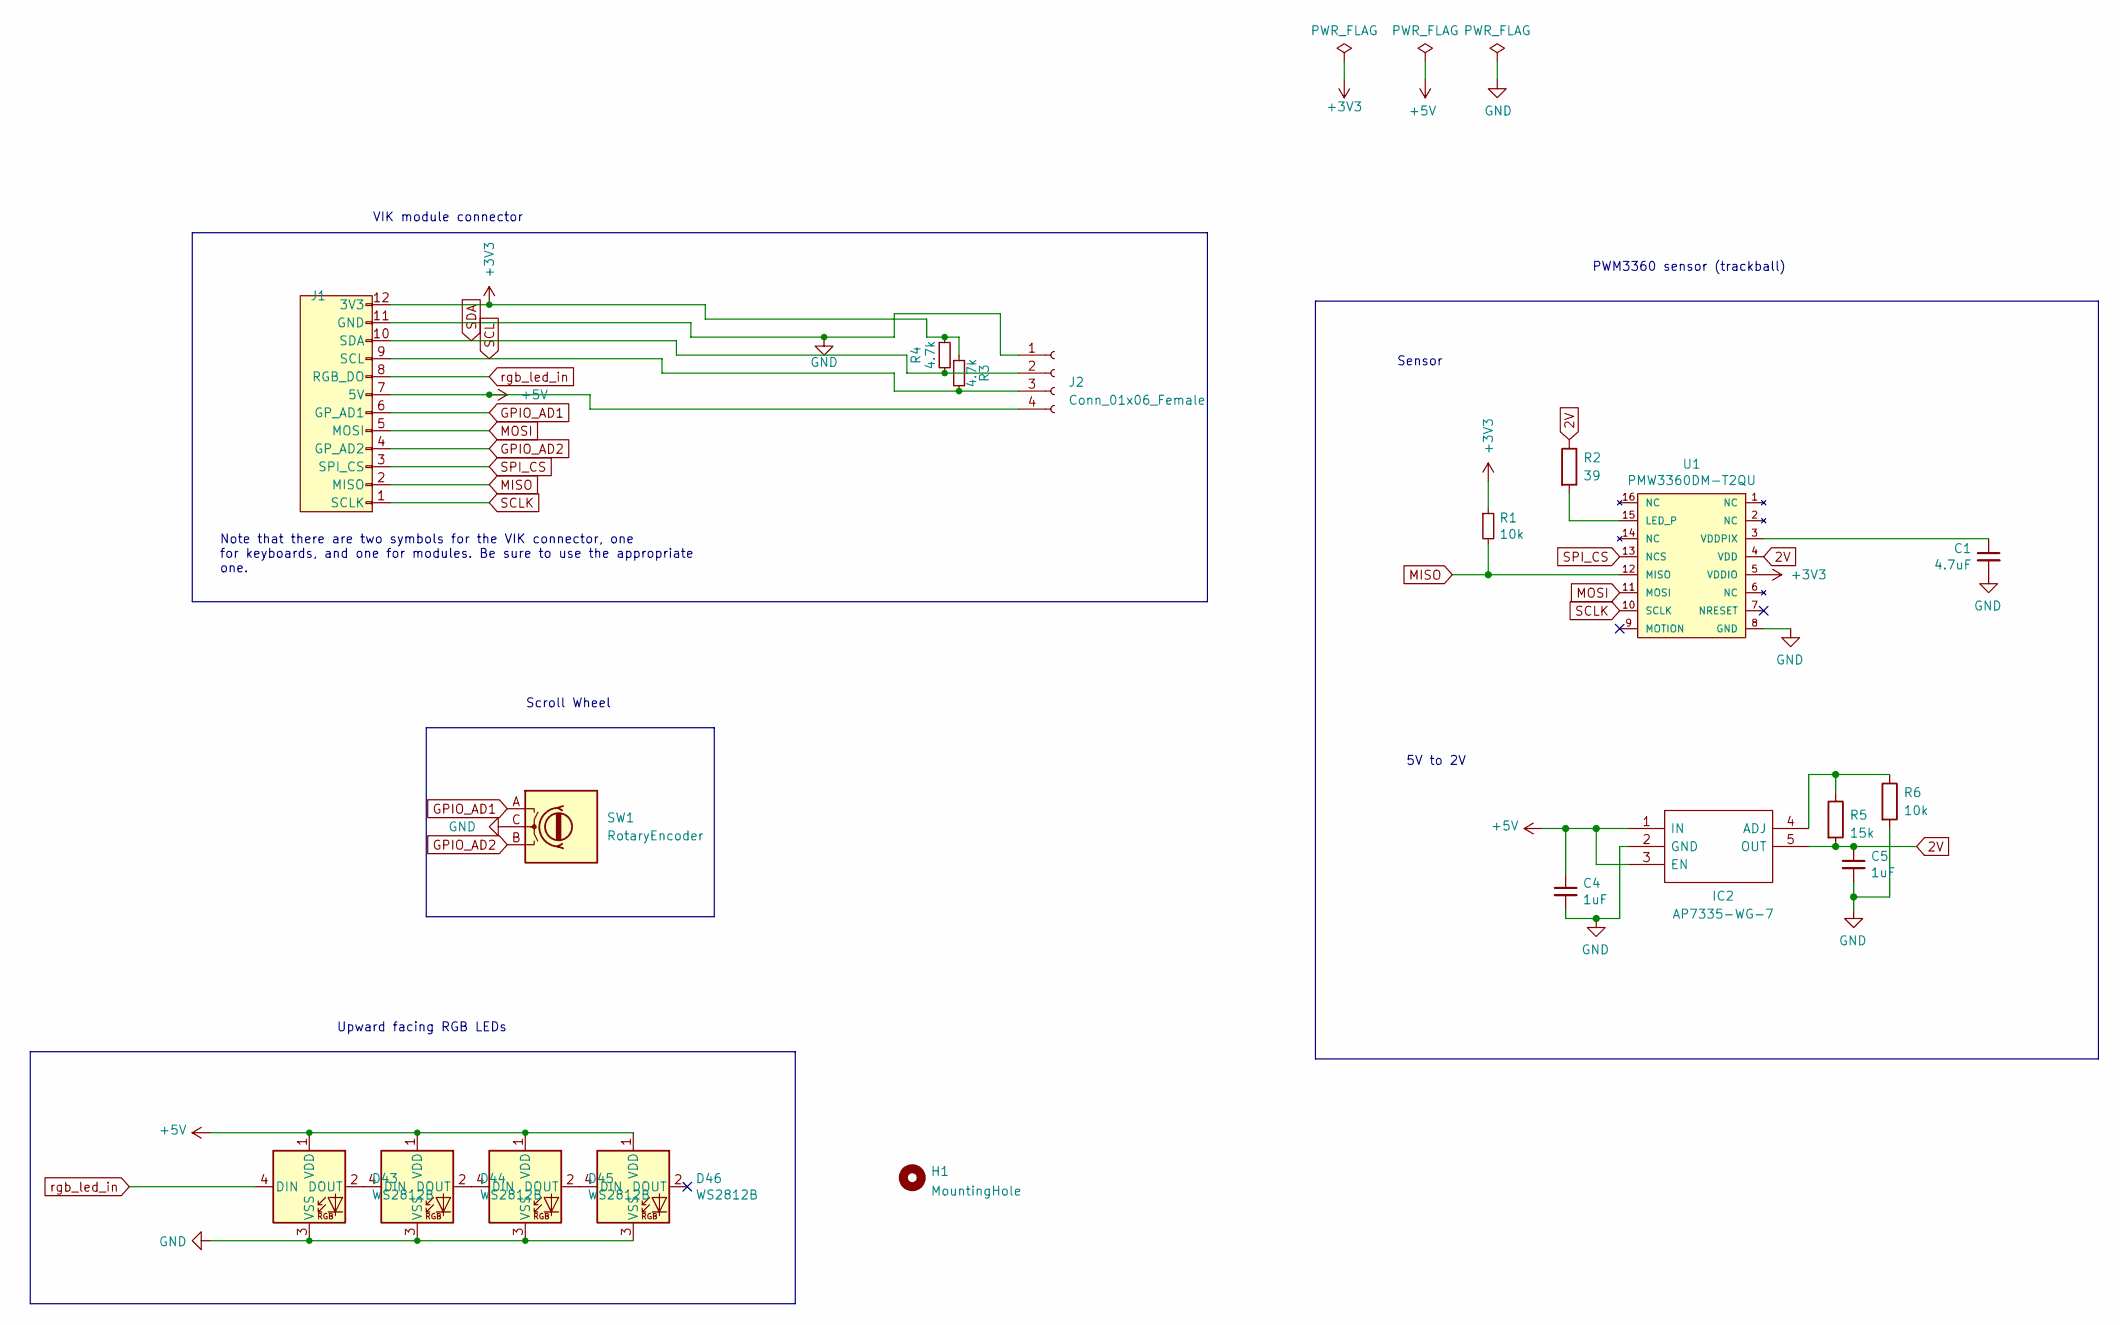
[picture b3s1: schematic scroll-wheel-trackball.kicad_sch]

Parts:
C1: 4.7uF; C_0603_1608Metric; LCSC C19666
C4, C5: 1uF; C_0603_1608Metric; LCSC C15849
D43, D44, D45, D46: WS2812B; LED_WS2812B_PLCC4_5.0x5.0mm_P3.2mm-reversible; LCSC C2761795
H1: MountingHole; vik-module-mounting-large
IC2: AP7335-WG-7; SOT-23-5_HandSoldering; Manufacturer_Part_Number AP7331-WG-7; Mouser Part Number 621-AP7331-WG-7
J1: vik-module-connector-horizontal; LCSC C479750
J2: Conn_01x06_Female; PinHeader_1x04_P2.54mm_Vertical
R1, R6: 10k; R_0603_1608Metric; LCSC C25804
R2: 39; R_0603_1608Metric; LCSC C23154
R3, R4: 4.7k; D3_TH_SMD
R5: 15k; R_0603_1608Metric; LCSC C22809
SW1: RotaryEncoder; PERS56v3
U1: PMW3360DM-T2QU; PMW3360

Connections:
2V: C5.1, IC2.5 (OUT), R2.1, R5.2, U1.4 (VDD)
+3V3: J1.12 (3V3), R1.1, R3.1, R4.1, U1.5 (VDDIO)
+5V: C4.1, D43.1 (VDD), D44.1 (VDD), D45.1 (VDD), D46.1 (VDD), IC2.1 (IN), IC2.3 (EN), J1.7 (5V), J2.4
GND: C1.2, C4.2, C5.2, D43.3 (VSS), D44.3 (VSS), D45.3 (VSS), D46.3 (VSS), IC2.2 (GND), J1.11 (GND), J2.1, R6.2, SW1.C, U1.8 (GND)
GPIO_AD1: J1.6 (GPIO_AD1), SW1.A
GPIO_AD2: J1.4 (GPIO_AD2), SW1.B
MISO: J1.2 (MISO), R1.2, U1.12 (MISO)
MOSI: J1.5 (MOSI), U1.11 (MOSI)
unnamed: D43.2 (DOUT), D44.4 (DIN)
unnamed: D44.2 (DOUT), D45.4 (DIN)
unnamed: D45.2 (DOUT), D46.4 (DIN)
unnamed: IC2.4 (ADJ), R5.1, R6.1
unnamed: R2.2, U1.15 (LED_P)
unnamed: C1.1, U1.3 (VDDPIX)
SCL: J1.9 (SCL), J2.3, R3.2
SCLK: J1.1 (SCLK), U1.10 (SCLK)
SDA: J1.10 (SDA), J2.2, R4.2
SPI_CS: J1.3 (SPI_CS), U1.13 (NCS)
rgb_led_in: D43.4 (DIN), J1.8 (RGB_LED_IN)

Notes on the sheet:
PWM3360 sensor (trackball)
Note that there are two symbols for the VIK connector, one for keyboards, and one for modules. Be sure to use the appropriate one.
Sensor
Upward facing RGB LEDs
5V to 2V
VIK module connector
Scroll Wheel

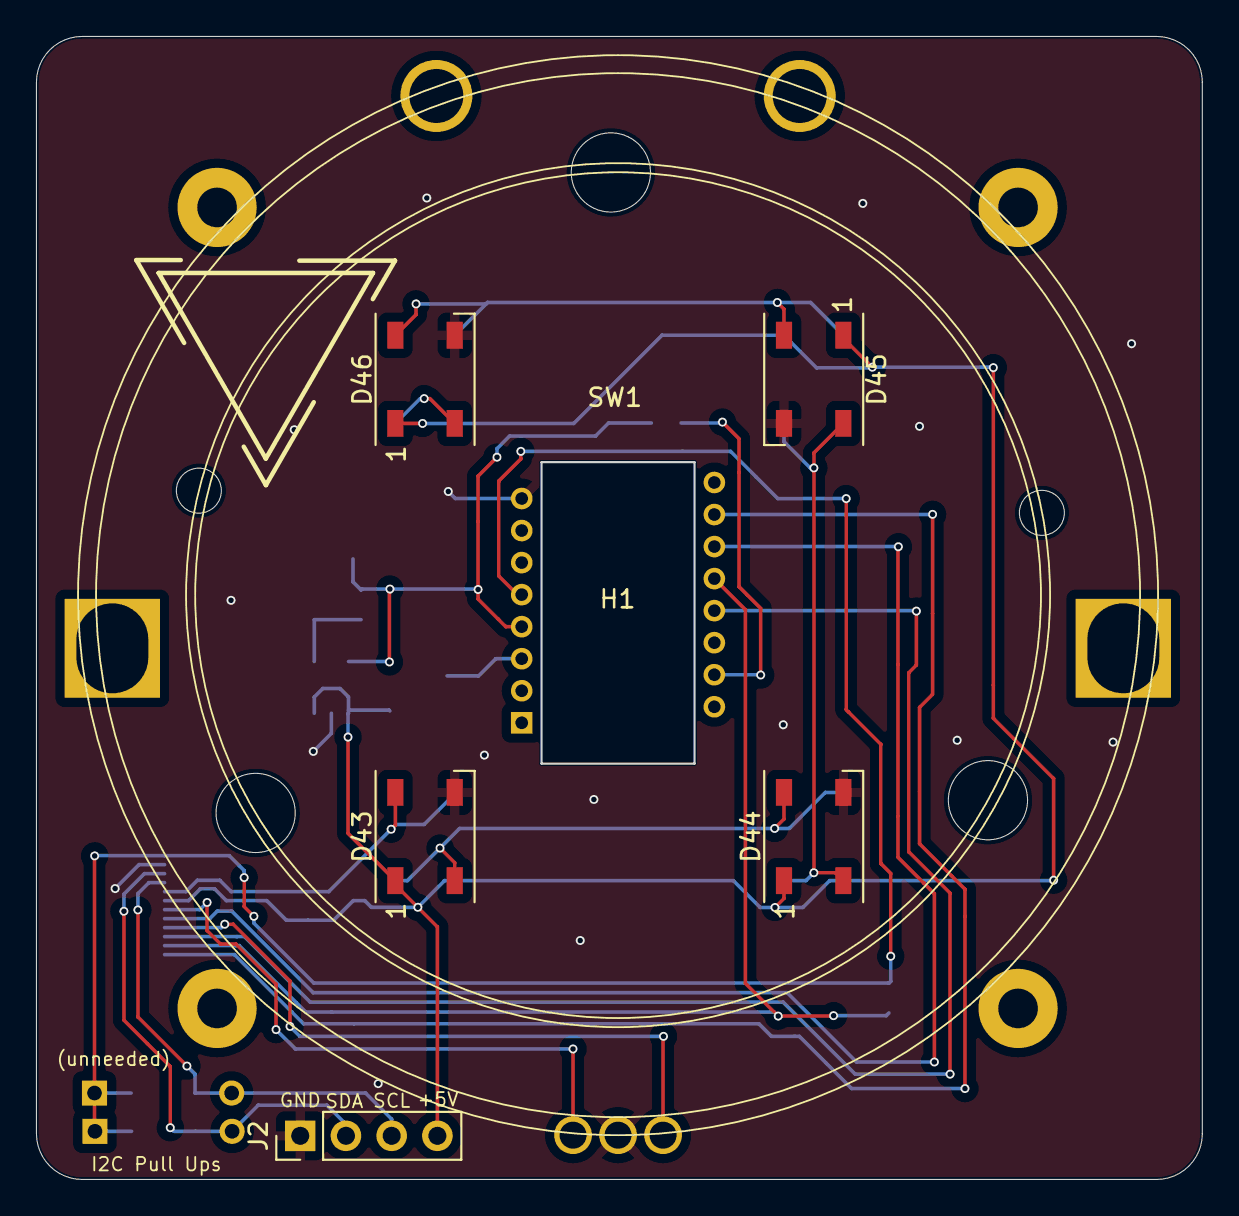
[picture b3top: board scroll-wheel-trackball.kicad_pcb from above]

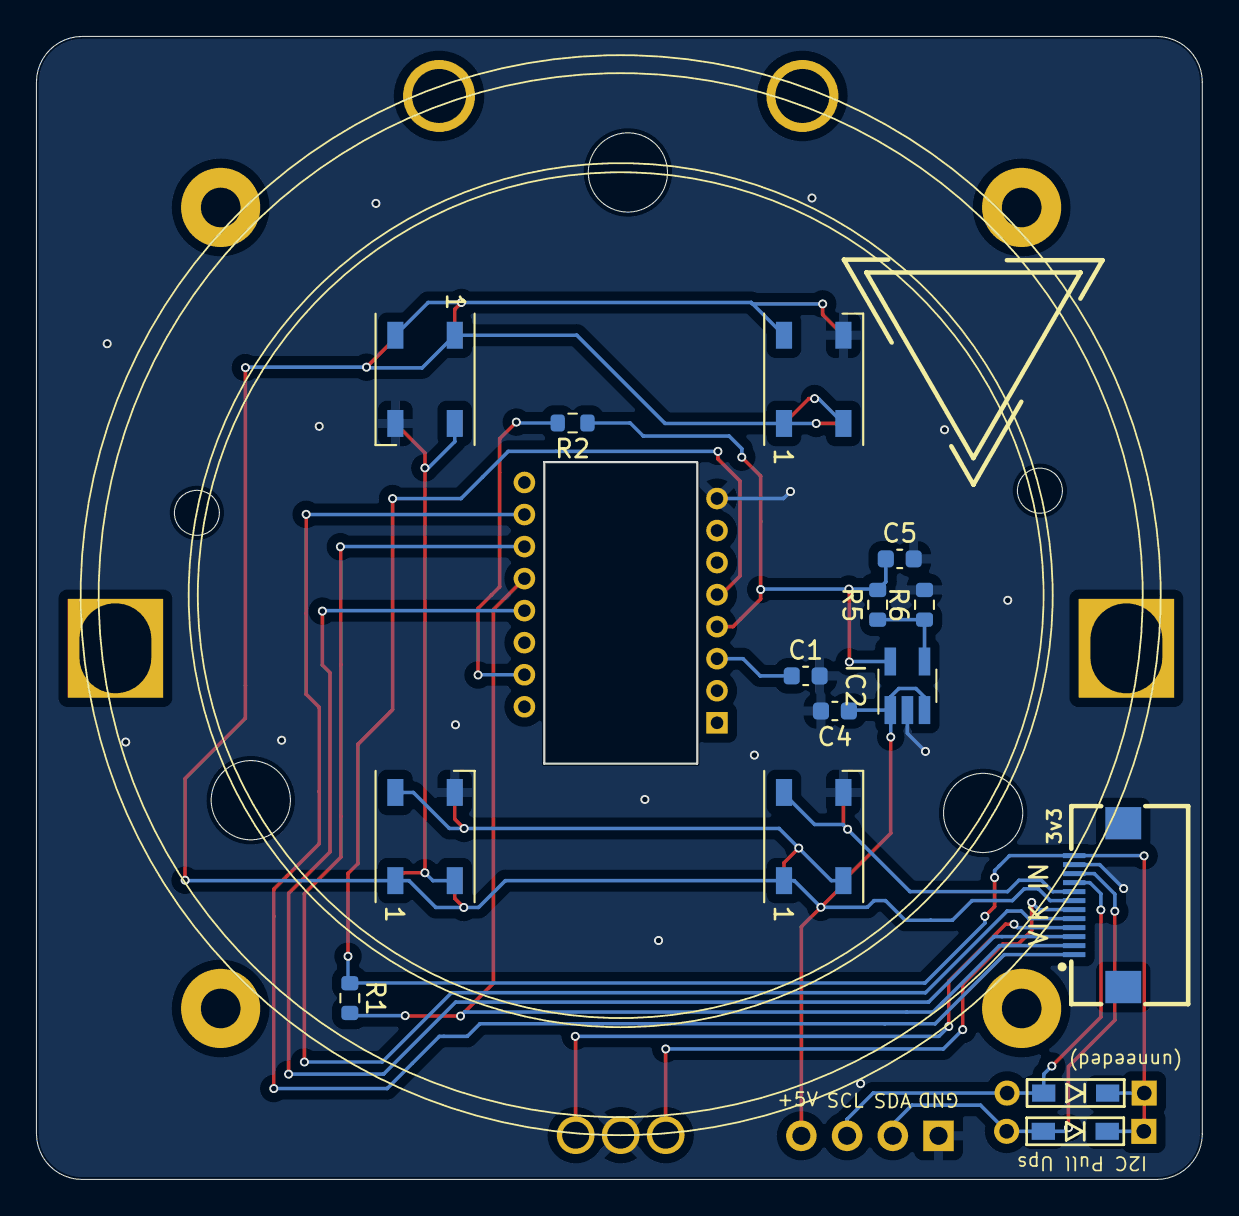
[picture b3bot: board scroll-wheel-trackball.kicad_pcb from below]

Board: 2 copper layers, 64.8 x 63.5 mm, 19 parts (12 on the bottom side), 19 nets.

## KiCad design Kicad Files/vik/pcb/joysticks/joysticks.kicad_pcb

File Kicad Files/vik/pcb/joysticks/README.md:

# joysticks vik module

## Overview

This is a vik module to support the following joysticks:  
* [adafruit 2765](https://www.adafruit.com/product/2765)
* [sparkfun 9032](https://www.sparkfun.com/products/9032)
* [nintendo joycon joystick](https://www.amazon.com/Replacement-Joystick-Nintendo-Original-Professional/dp/B08397JQZG/)

Please note that this PCB does **not** support the click on the sparkfun analog joystick, only x and y movements

## Fabrication and BOM

For PCB fabrication, you can use the files in the production folder.

* gerbers.zip - the file used to fabricate the pcb
* bom.csv - used for PCBA. You can also use the part numbers in this file to look up the exact parts as [lcsc.com](https://lcsc.com)
* positions.csv - used for PCBA

Using the 3 files above, this has been tested at [jlcpcb.com](https://jlcpcb.com)

## VIK module certification

| Category                | Classification          | Response           |
| ----------------------- | ----------------------- | ------------------ |
| FPC connector           | Required                | :heavy_check_mark: |
| Breakout pins           | Recommended             | :x:                |
| Uses: SPI               | Optional                | :x:                |
| SPI used for SPI only   | Strongly recommended    | N/A                |
| Uses: I2C               | Optional                | :x:                |
| I2C used for I2C only   | Strongly Recommended    | :x:                |
| I2C pull ups            | Required                | N/A                |
| Uses: RGB               | Optional                | :x:                |
| Uses: Extra GPIO 1      | Optional                | :heavy_check_mark: |
| Uses: Extra GPIO 2      | Optional                | :heavy_check_mark: |
| Standard PCB Size/Mount | Strongly recommended    | :x:                |

## PCB images

## joycon joystick wiring

Caution: I have not tested the joycon joystick, but I wired per the image below  

I got this diagram from here:  
https://sudomod.com/forum/viewtopic.php?t=3485

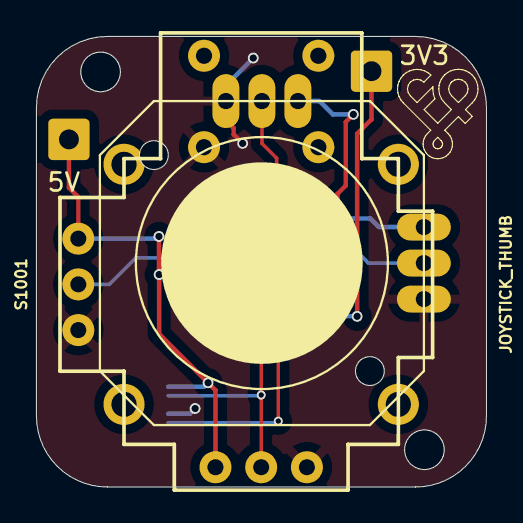
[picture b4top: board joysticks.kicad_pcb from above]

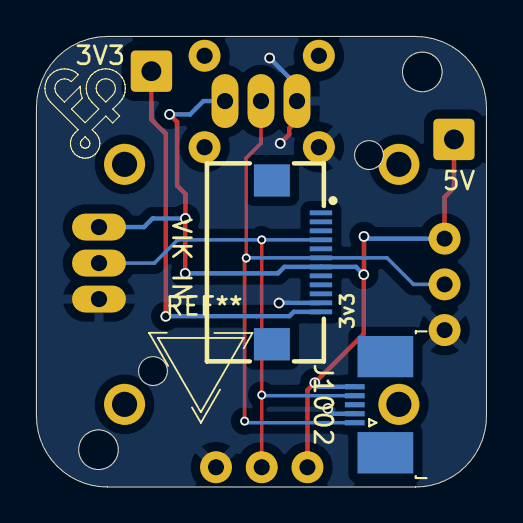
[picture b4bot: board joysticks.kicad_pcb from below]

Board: 2 copper layers, 25.0 x 25.0 mm, 6 parts (2 on the bottom side), 5 nets.

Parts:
J1001, J1007: Conn_01x01_Socket; SolderWire-0.5sqmm_1x01_D0.9mm_OD2.3mm
J1002: Conn_01x05_Socket; TE_0-1734839-5_1x05-1MP_P0.5mm_Horizontal
J1003: vik-module-connector-horizontal
JOY1001: JOYSTICK_ANALOG_XY; joystick_analog_xy
S1001: JOYSTICK_THUMB; sparkfun_9032_joystick_thumb

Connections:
GND: J1002.2, J1003.11 (GND), JOY1001.X- (A), JOY1001.Y- (A), S1001.B2A (SEL-), S1001.H3 (H-), S1001.V3 (V-)
GPIO_AD1: J1002.1, J1003.6 (GPIO_AD1), JOY1001.X (S), S1001.V2 (V)
GPIO_AD2: J1002.4, J1003.4 (GPIO_AD2), JOY1001.Y (S), S1001.H2 (H)
VDD_3.3V: J1001.1, J1003.12 (3V3)
VDD_5V: J1002.5, J1003.7 (5V), J1007.1, JOY1001.X+ (E), JOY1001.Y+ (E), S1001.H1 (H+), S1001.V1 (V+)

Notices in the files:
Kicad Files/vik/pcb/pmw3360-xs/pmw3360.kicad_sch:
Copyright Quentin Lebastard
